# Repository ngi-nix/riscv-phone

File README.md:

# RISC-V Phone

This flake packages the firmware for the Freedom E310 and the Espressif ESP32 SoCs.

It is currently based against $HEAD of upstream for the [source files](http://majstor.org/gitweb/?p=rvPhone.git;a=tree).

If anything breaks, you can always pin the `riscvphone-src` input to a working revision:

```
url = "git://majstor.org/rvPhone.git?rev=38e19a65fda7a37688320b4b732eb1113bbcbad7";
```
You may find more information about this project [here](http://majstor.org/rvphone/) and [here](http://majstor.org/rvphone/build.html).

For further details, please refer to the documentation in the flake itself.

## Building

To build the firmware for each SoC (and possibly also flash it), type `nix build .#fe310` or `nix build .#esp32`.

## Developing

You can enter a developer shell by typing `nix develop .#fe310` or `nix develop .#esp32`. 

Navigate into `fw/fe310` or `fw/esp32` and type `make` to compile. Typing `make clean` will delete the compiled files.

When typing `make` in `fw/esp32`, a configuration menu will open if no `sdkconfig` configuration file exists, even if empty. You can manually choose the configuration values in this menu at any time by typing `make menuconfig` or pass them automatically via the [sdkconfig.defaults](https://docs.espressif.com/projects/esp-idf/en/latest/esp32/api-reference/kconfig.html#using-sdkconfig-defaults) file.

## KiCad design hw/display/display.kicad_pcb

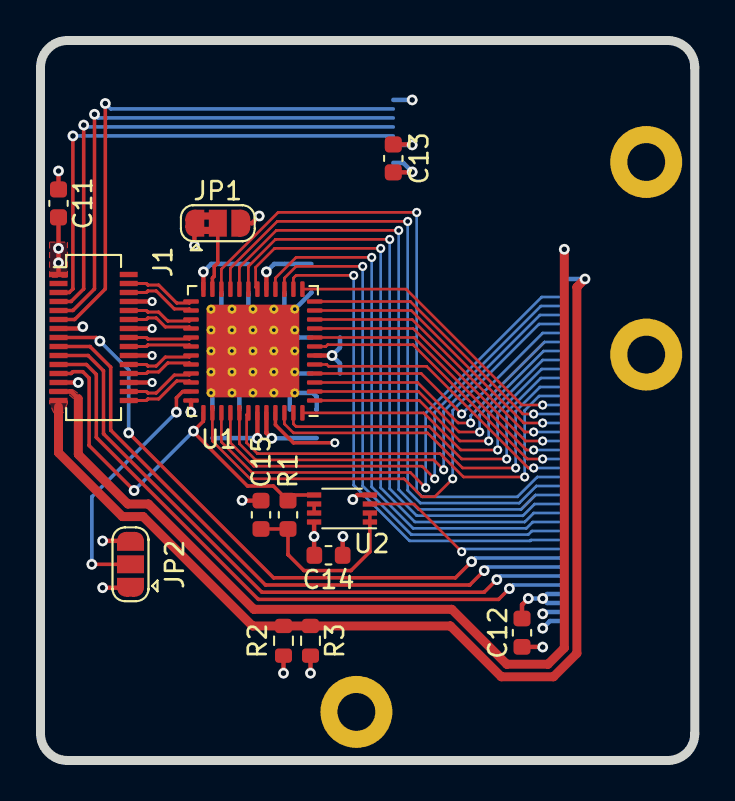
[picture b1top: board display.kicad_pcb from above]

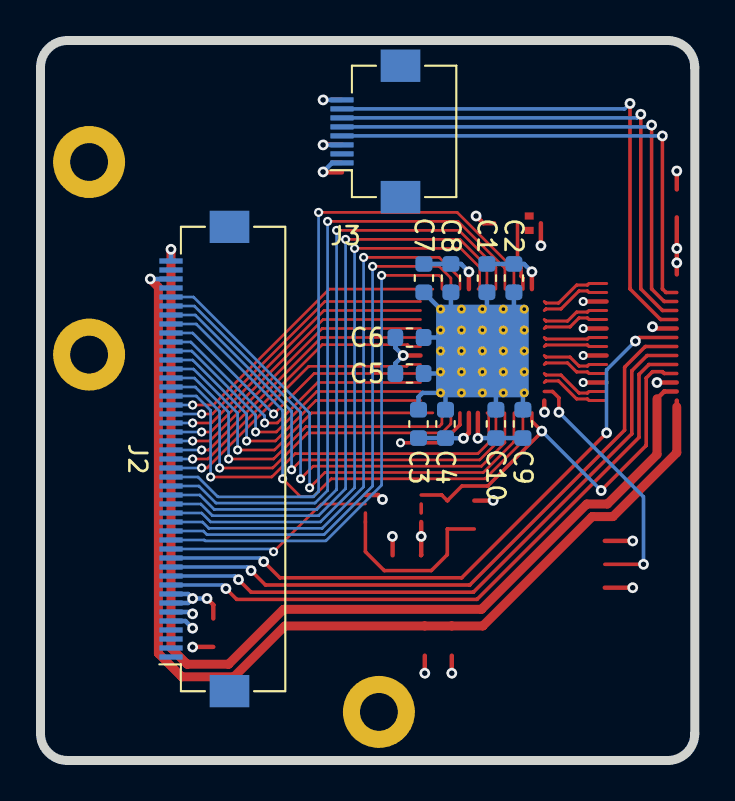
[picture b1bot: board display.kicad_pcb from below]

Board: 4 copper layers, 36.3 x 40.0 mm, 28 parts (12 on the bottom side), 56 nets.

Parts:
C1, C3, C5, C7, C9, C12, C13, C14, C15: 0.1uF; C_0603_1608Metric
C2, C4, C6, C8, C10: 0.01uF; C_0603_1608Metric
C11: 10uF; C_0603_1608Metric
J1: Input; Molex_SlimStack_55560-0301_2x15_P0.50mm_Vertical
J2: Display; Hirose_FH12-45S-0.5SH_1x45-1MP_P0.50mm_Horizontal
J3: Touch; Hirose_FH12-8S-0.5SH_1x08-1MP_P0.50mm_Horizontal
J4, J5, J6: Spacer
JP1: CLK_POL; SolderJumper-3_P1.3mm_Bridged2Bar12_RoundedPad1.0x1.5mm
JP2: SLEW; SolderJumper-3_P1.3mm_Open_RoundedPad1.0x1.5mm
R1: 10K; R_0603_1608Metric
R2, R3: DNP; R_0603_1608Metric
U1: SN65LVDS822; QFN-48-1EP_7x7mm_P0.5mm_EP5.15x5.15mm_ThermalVias
U2: 74AUP2G132DC; VSSOP-8_2.3x2mm_P0.5mm

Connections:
+3V3: C1.1, C2.1, C3.1, C4.1, C5.1, C6.1, C7.1, C8.1, C9.1, C10.1, C11.1, C12.1, C13.1, C14.1, J1.1, J2.7, J2.8, J3.3, JP1.1, JP2.1, U1.6, U1.17, U1.24, U1.43, U1.44, U2.8
/DISP_B0: J2.37, U1.4
/DISP_B1: J2.36, U1.3
/DISP_B2: J2.35, U1.2
/DISP_B3: J2.34, U1.1
/DISP_B4: J2.33, U1.48
/DISP_B5: J2.32, U1.47
/DISP_B6: J2.31, U1.46
/DISP_B7: J2.30, U1.42
/DISP_DE: J2.38, U1.38
/DISP_G0: J2.29, U1.13
/DISP_G1: J2.28, U1.12
/DISP_G2: J2.27, U1.11
/DISP_G3: J2.26, U1.10
/DISP_G4: J2.25, U1.9
/DISP_G5: J2.24, U1.8
/DISP_G6: J2.23, U1.7
/DISP_G7: J2.22, U1.5
/DISP_HSYNC: J2.40, U1.40
/DISP_PCLK: J2.39, U1.41
/DISP_R0: J2.21, U1.22
/DISP_R1: J2.20, U1.21
/DISP_R2: J2.19, U1.20
/DISP_R3: J2.18, U1.19
/DISP_R4: J2.17, U1.18
/DISP_R5: J2.16, U1.16
/DISP_R6: J2.15, U1.15
/DISP_R7: J2.14, U1.14
/DISP_RST: J2.13, U2.3
/DISP_VSYNC: J2.41, U1.39
/LVDS_A0N: J1.4, U1.25
/LVDS_A0P: J1.6, U1.26
/LVDS_A1N: J1.10, U1.27
/LVDS_A1P: J1.12, U1.28
/LVDS_A2N: J1.16, U1.29
/LVDS_A2P: J1.18, U1.30
/LVDS_A3N: J1.28, U1.33
/LVDS_A3P: J1.30, U1.34
/LVDS_CLKN: J1.22, U1.31
/LVDS_CLKP: J1.24, U1.32
CTP.INT: J1.9, J3.6
CTP.RST: J1.11, J3.7
CTP.SCL: J1.5, J3.4
CTP.SDA: J1.7, J3.5
ENABLE: J1.23, R1.2, U1.37, U2.5
GND: C1.2, C2.2, C3.2, C4.2, C5.2, C6.2, C7.2, C8.2, C9.2, C10.2, C11.2, C12.2, C13.2, C14.2, C15.2, J1.8, J1.13, J1.14, J1.20, J1.25, J1.26, J2.5, J2.6, J3.1, J3.8, J4.1, J5.1, J6.1, JP1.3, JP2.3, R2.2, R3.2, U1.36, U1.45, U1.49, U2.4
LED_A: J1.27, J2.45
LED_K: J1.29, J2.43, R2.1, R3.1
unnamed: C15.1, R1.1, U2.1, U2.2
unnamed: JP1.2, U1.23
unnamed: JP2.2, U1.35
unnamed: U2.6, U2.7
SPI.CS: J1.15, J2.12
SPI.MISO: J1.21, J2.9
SPI.MOSI: J1.19, J2.10
SPI.SCK: J1.17, J2.11

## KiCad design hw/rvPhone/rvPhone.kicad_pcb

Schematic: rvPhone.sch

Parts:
C1: 1uF; C_0603_1608Metric
C2: 0.047uF; C_0603_1608Metric
C3: 4.7uF; C_0603_1608Metric
C4, C5, C6, C7, C8, C9, C10, C11, C21, C22, C36, C38, C41, C42, C50, C53, C54: 10uF; C_0603_1608Metric
C12: 47uF; C_0805_2012Metric
C13, C15, C16, C17, C18, C19, C20, C23, C24, C27, C28, C29, C30, C31, C32, C33, C34, C35, C37, C39, C40, C43, C44, C45, C46: 0.1uF; C_0603_1608Metric
C14: 0.01uF; C_0603_1608Metric
C25, C26: 10pF; C_0603_1608Metric
C51, C52, C55: 22uF; C_0805_2012Metric
D1: B5817WS; D_SOD-323
D2: LED; LED_0603_1608Metric
J1: USB_OTG; GCT_MicroUSB-USB3080
J2: BATT; PinHeader_1x02_P2.54mm_Vertical
J3: +5V; PinHeader_1x02_P2.54mm_Vertical
J4: AudioJack; 35RASMT4BHNTRX
J5: SPEAKER; PinHeader_1x04_P2.54mm_Vertical
J6: Ext Audio; Molex_SlimStack_54722-0164_2x08_P0.50mm_Vertical
JP1: AUDIO PWR; SolderJumper-3_P1.3mm_Open_RoundedPad1.0x1.5mm
L1: 2.2uH; L_Vishay_IHLP-2525
L2: 2.2uH; Coilcraft-LPS3015
L3: 1uH; Coilcraft-XAL40
R1: 260R; R_0603_1608Metric
R2: 5.23K; R_0603_1608Metric
R3: 30.1K; R_0603_1608Metric
R4: 2.2K; R_0603_1608Metric
R5: 560K; R_0603_1608Metric
R6: 180K; R_0603_1608Metric
R7, R8, R9, R10, R11, R15, R16, R18, R19, R20, R21, R22, R23, R24, R25, R26, R30, R34, R35: 100K; R_0603_1608Metric
R12: 100R; R_0603_1608Metric
R13, R14, R33: 10K; R_0603_1608Metric
R17, R28, R29: 47K; R_0603_1608Metric
R27: 210K; R_0603_1608Metric
R31: 50K; R_0603_1608Metric
R32: 0R; R_0603_1608Metric
SW1: RESET; SW_SPST_PTS810
SW2: WAKE; Panasonic_EVPAE
TP2: PMU_OUT0; TestPoint_Pad_D1.5mm
U1: BQ25895; Texas_S-PWQFN-N24_EP2.7x2.7mm_ThermalVias
U2: TPS62293; TPS62290
U3: TPS630250
U4: FE310-G002; QFN-48-1EP_6x6mm_P0.4mm_EP4.2x4.2mm_ThermalVias
U5: IS25LP128-JKLE; WSON-8-1EP_6x5mm_P1.27mm_EP3.4x4mm
U6: SN74LVC2G07DCK; Texas_R-PDSO-G6
U7: TMUX1574RSV; UQFN-16_1.8x2.6mm_P0.4mm
U8, U9: 74HC00; DHVQFN-14_2.5x3.0mm_P0.5mm_EP1.0x1.5mm
U10, U11: 74HC595; DHVQFN-16_2.5x3.5mm_P0.5mm_EP1.0x2.0mm
U12: ICS-43434
U13, U14: MAX98357A; TQFN-16-1EP_3x3mm_P0.5mm_EP1.23x1.23mm_ThermalVias
U15, U16: MAX14689A; TDFN-10-1EP_2x2.5mm_P0.4mm_EP1.3x1.4mm_ThermalVias
U17: SN74LVC1G04DCK; Texas_R-PDSO-G5
U18: TMUX1119DCK; Texas_R-PDSO-G6
U19: 74LVC1G02; Texas_R-PDSO-G5
U20: SN74LVC2G66DCU; VSSOP-8_2.3x2mm_P0.5mm
X1: SiT1533
Y1: 16MHz; TXC_7M

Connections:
+1V8: C9.1, C19.1, C20.1, C21.1, C55.1, L2.2, R12.1, U2.3 (FB), U4.6 (VDD), U4.30 (VDD), U4.46 (VDD); also elsewhere on the board
+VSYS: C4.1, C5.1, C8.1, C10.1, D2.2 (A), L1.2, U1.8 (OTG), U1.15 (SYS), U1.16 (SYS), U2.4 (EN), U2.5 (VIN), U3.4 (VIN), U3.5 (VIN), U3.6 (VIN), U3.7 (VINA), U3.8 (EN); also elsewhere on the board
/AON_PMU_OUT_0: TP2.1, U4.22 (AON_PMU_OUT_0)
/AON_PMU_OUT_1: U4.17 (AON_PMU_OUT_1)
/AUDIO_OUT_L+: U13.9 (OUTP), U15.3
/AUDIO_OUT_L-: U13.10 (OUTN), U15.10
/AUDIO_OUT_R+: U14.9 (OUTP), U16.3
/AUDIO_OUT_R-: U14.10 (OUTN), U16.10
/BQ_QON: U1.12 (/QON), U6.4 (2Y)
/BQ_SW: C2.1, D1.2 (A), L1.1, U1.19 (SW), U1.20 (SW)
/EXT_AUDIO_EN: J6.10, U19.4
/HP_DET: J4.RN, J4.TN, R30.1, U17.2 (A)
/HP_L: C42.2, U15.5
/HP_R: C41.2, U16.5
/MIC_CLK: R23.2, U7.11 (S4B), U8.1, U9.12, U9.13, U12.4 (SCK)
/MIC_SD: U12.6 (SD), U20.2
/MIC_WS: R21.2, U7.1 (S1B), U12.1 (WS)
/PLL_AVDD: C23.1, C24.1, R12.2, U4.7 (PLL_AVDD)
/PLL_AVSS: C23.2, C24.2, U4.8 (PLL_AVSS)
/PSD_LFALTCLK: U4.20 (AON_PSD_LFALTCLK), X1.3 (CLKOUT)
/QSPI_CLK: U4.48 (QSPI_CLK), U5.6 (SCK)
/QSPI_CS: R8.2, U4.5 (QSPI_CS), U5.1 (S#)
/QSPI_DQ_0: U4.4 (QSPI_DQ_0), U5.5 (MOSI/IO0)
/QSPI_DQ_1: U4.3 (QSPI_DQ_1), U5.2 (MISO/IO1)
/QSPI_DQ_2: U4.2 (QSPI_DQ_2), U5.3 (WP#/IO2)
/QSPI_DQ_3: R9.2, U4.1 (QSPI_DQ_3), U5.7 (HOLD#/IO3)
/RESET: C14.1, R10.1, SW1.2, U4.24 (AON_ERST_N), U6.6 (1Y)
/SD_IN: U7.4 (S2B), U11.9, U13.1 (DIN), U14.1 (DIN)
/SD_OUT: R22.2, U7.8 (S3B), U10.14, U20.1
/SPK_CLK: U9.11, U13.16 (BCLK), U14.16 (BCLK)
/SPK_EN: C39.1, C40.1, R27.2, U7.15 (SEL), U8.8, U9.4, U9.5, U13.4 (SD_MODE), U15.2, U16.2, U19.1
/SPK_GAIN: U13.2 (GAIN_SLOT), U14.2 (GAIN_SLOT), U18.5
/SPK_GAIN_SEL: U9.8, U18.1
/SPK_L+: J5.1, J6.5, J6.7, U15.1
/SPK_L-: J5.2, J6.9, J6.11, U15.8
/SPK_R+: J5.3, U16.1
/SPK_R-: J5.4, U16.8
/XTAL_XI: C25.1, U4.9 (16M_XTAL_XI), Y1.1
/XTAL_XO: C26.1, U4.10 (16M_XTAL_XO), Y1.2
/~HP_DET: U9.9, U15.7, U16.7, U17.4 (Y)
BQ.INT: U1.7 (INT); also elsewhere on the board
BT81X.AUDIO: J6.6; also elsewhere on the board
BT81X.GPIO2: U9.10, U19.2; also elsewhere on the board
BT81X.INT: R16.1, U7.12 (S4A); also elsewhere on the board
CTP.RST: R15.1, U7.16 (S1A); also elsewhere on the board
DISP_CS: U9.3; also elsewhere on the board
GND: C1.2, C3.2, C4.2, C5.2, C6.2, C7.2, C8.2, C9.2, C10.2, C11.2, C12.2, C13.2, C14.2, C15.2, C16.2, C17.2, C18.2, C19.2, C20.2, C21.2, C22.2, C25.2, C26.2, C27.2, C28.2, C29.2, C30.2, C31.2, C32.2, C33.2, C34.2, C35.2, C36.2, C37.2, C38.2, C39.2, C40.2, C43.2, C44.2, C45.2, C46.2, C50.2, C51.2, C52.2, C53.2, C54.2, C55.2, J1.5 (GND), J2.2, J3.2, J4.S, J6.1, J6.3, R1.2, R3.2, R6.2, R18.1, R19.1, R20.1, R21.1, R22.1, R23.1, R26.1, R28.2, R29.2, R32.2, R33.2, R34.1, R35.1, SW1.1, SW2.1, U1.9 (/CE), U1.17 (PGND), U1.18 (PGND), U1.25 (EP), U2.2 (MODE), U2.6 (GND), U2.7 (EP), U3.2 (PGND), U3.9 (GND), U3.10 (PFM), U4.21 (AON_PSD_LFCLKSEL), U4.49 (GND), U5.4 (VSS), U5.9 (EP), U6.2 (GND), U7.6 (GND), U7.13 (/EN), U8.7 (GND), U8.15, U9.7 (GND), U9.15, U10.8, U10.12, U10.17, U11.8, U11.12, U11.17, U12.2 (LR), U12.3 (GND), U13.3 (GND), U13.11 (GND), U13.15 (GND), U13.17 (EP), U14.3 (GND), U14.11 (GND), U14.15 (GND), U14.17 (EP), U15.4, U15.9, U15.11, U16.4, U16.9, U16.11, U17.3 (GND), U18.3, U19.3, U20.3, U20.4, U20.5, U20.6, X1.2 (GND), Y1.3; also elsewhere on the board
GPIO_0: U4.25 (GPIO_0/PWM0.0); also elsewhere on the board
GPIO_16: U4.38 (GPIO_16/UART0.RX), U7.7 (D3)
GPIO_17: U4.39 (GPIO_17/UART0.TX), U7.5 (D2)
GPIO_18: R19.2, U4.40 (GPIO_18), U8.5, U8.12, U8.13
GPIO_20: U4.42 (GPIO_20/PWM1.0); also elsewhere on the board
GPIO_22: U4.44 (GPIO_22/PWM1.3); also elsewhere on the board
GPIO_23: R18.2, U4.45 (GPIO_23); also elsewhere on the board
I2C0.SCL: R13.2, U1.5 (SCL), U4.37 (GPIO_13/PWM2.3); also elsewhere on the board
I2C0.SDA: R14.2, U1.6 (SDA), U4.36 (GPIO_12/PWM2.2); also elsewhere on the board
JTAG_TCK: U4.13 (JTAG_TCK); also elsewhere on the board
JTAG_TDI: U4.16 (JTAG_TDI); also elsewhere on the board
JTAG_TDO: U4.14 (JTAG_TDO); also elsewhere on the board
JTAG_TMS: U4.15 (JTAG_TMS); also elsewhere on the board
JTAG_TRST_N: R7.2, U6.1 (1A); also elsewhere on the board
unnamed: C2.2, U1.21 (BTST)
unnamed: C3.1, R2.1, U1.22 (REGN)
unnamed: C6.1, C7.1, J2.1, U1.13 (BAT), U1.14 (BAT)
unnamed: C41.1, J4.R, R28.1
unnamed: C42.1, J4.T, R29.1
unnamed: D2.1 (K), R4.2
unnamed: L2.1, U2.1 (SW)
unnamed: L3.1, U3.3 (L1)
unnamed: L3.2, U3.1 (L2)
unnamed: R1.1, U1.10 (ILIM)
unnamed: R2.2, R3.1, R33.1, U1.11 (TS)
unnamed: R4.1, U1.4 (STAT)
unnamed: R5.2, R6.1, U3.11 (FB)
unnamed: R27.1, U14.4 (SD_MODE)
unnamed: R31.2, U18.6
unnamed: R32.1, U18.4
unnamed: U1.2 (D+), U1.3 (D-)
unnamed: U8.3, U8.4
unnamed: U8.10, U8.11
unnamed: U9.2, U9.6
unnamed: U10.9, U11.14
unnamed: U8.6, U10.11, U11.11
PWM0.1: U4.26 (GPIO_1/PWM0.1), U7.10 (D4)
PWM1.1: U4.41 (GPIO_19/PWM1.1), U7.2 (D1)
PWM1.2: R17.2, U4.43 (GPIO_21/PWM1.2), U8.2, U8.9, U20.7
PWM2.1: R20.2, U4.35 (GPIO_11/PWM2.1), U9.1, U13.14 (LRCLK), U14.14 (LRCLK)
SPI1.MISO: R24.2, U4.29 (GPIO_4/SPI1.MISO); also elsewhere on the board
SPI1.MOSI: R25.2, U4.28 (GPIO_3/SPI1.MOSI/PWM0.3); also elsewhere on the board
SPI1.SCK: R26.2, U4.31 (GPIO_5/SPI1.SCK); also elsewhere on the board
SPI1.SS0: U4.27 (GPIO_2/SPI1.SS0/PWM0.2); also elsewhere on the board
SPI1.SS2: U4.33 (GPIO_9/SPI1.SS2); also elsewhere on the board
SPI1.SS3: U4.34 (GPIO_10/SPI1.SS3/PWM2.0); also elsewhere on the board
UART0.RXD: R35.2, U7.9 (S3A); also elsewhere on the board
UART0.TXD: R34.2, U7.3 (S2A); also elsewhere on the board
USB_D+: J1.3 (D+); also elsewhere on the board
USB_D-: J1.2 (D-); also elsewhere on the board
VBUS: C1.1, C50.1, J1.1 (VBUS), U1.1 (VBUS); also elsewhere on the board
WAKE: R11.1, SW2.2, U4.18 (AON_PMU_DWAKEUP_N), U6.3 (2A); also elsewhere on the board

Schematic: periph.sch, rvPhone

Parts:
C201, C204, C205, C206, C207, C208, C209, C210, C211, C212, C213, C214, C219, C220, C223, C224, C226, C227, C229, C230, C231: 0.1uF; C_0603_1608Metric
C202, C228: 22uF; C_0805_2012Metric
C203, C221, C222: 1uF; C_0603_1608Metric
C215, C216, C217: 33pF; C_0603_1608Metric
C218: 470uF; CP_EIA-7343-31_Kemet-D
C225: 0.01uF; C_0603_1608Metric
J201: Modem; TE_mPCIe-1775862
J202: SIM_Card; Wurth_NanoSIM-693043020611
J203: Motor; SolderWirePad_1x02_SMD_1x2mm
J204: Micro_SD_Card_Det; Molex_MicroSD-5027740891
J205: Prog; Hirose_FH12-12S-0.5SH_1x12-1MP_P0.50mm_Horizontal
J206: Expansion; Molex_SlimStack_54722-0164_2x08_P0.50mm_Vertical
J207: Camera; Molex_SlimStack_54722-0164_2x08_P0.50mm_Vertical
J208, J209: Spacer; Spacer_small
JP201: PCM_EN; SolderJumper-3_P1.3mm_Bridged2Bar12_RoundedPad1.0x1.5mm
JP202: SIMCom_EN; SolderJumper-3_P1.3mm_Bridged2Bar12_RoundedPad1.0x1.5mm
JP203: Q.DTR; SolderJumper-2_P1.3mm_Open_RoundedPad1.0x1.5mm
JP204: Q.RI; SolderJumper-2_P1.3mm_Open_RoundedPad1.0x1.5mm
JP205: Q.RXD; SolderJumper-2_P1.3mm_Open_RoundedPad1.0x1.5mm
JP206: Q.TXD; SolderJumper-2_P1.3mm_Open_RoundedPad1.0x1.5mm
R201, R209: 10K; R_0603_1608Metric
R202, R203, R207: 47K; R_0603_1608Metric
R204, R205, R206: 22R; R_0603_1608Metric
R208: 4.7K; R_0603_1608Metric
SW201: ESP32_RST; SW_SPST_PTS810
SW202: MODEM_RST; SW_SPST_PTS810
U201: ESP32-WROOM
U202: SN74CBTLV3125RGY; Texas_S-PVQFN-N14_ThermalVias
U203, U204: TXB0104RGY; Texas_S-PVQFN-N14_ThermalVias
U205: DRV2605LDGS; VSSOP-10_3x3mm_P0.5mm
U206: LSM9DS1; LGA-24L_3x3.5mm_P0.43mm
U207: FT230XQ; QFN-16-1EP_4x4mm_P0.65mm_EP2.1x2.1mm
U208: TMUX154ERSW; UQFN-10_1.4x1.8mm_P0.4mm

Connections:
+1V8: C206.1, C208.1, JP201.1, JP202.1, U203.1 (VCCA), U204.1 (VCCA); also elsewhere on the board
+VSYS: J207.2, J207.4; also elsewhere on the board
/periph/ESP32_EN: C203.1, C219.1, R201.2, SW201.1, U201.3 (EN)
/periph/ESP32_PCM_CLK: U201.9 (IO33), U203.13 (B1)
/periph/ESP32_PCM_DI: U201.6 (IO34), U203.12 (B2)
/periph/ESP32_PCM_DO: U201.24 (IO2), U203.11 (B3)
/periph/ESP32_PCM_SYNC: U201.26 (IO4), U203.10 (B4)
/periph/ESP32_UART2_DTR: JP203.1, U201.8 (IO32), U204.12 (B2)
/periph/ESP32_UART2_RI: JP204.1, U201.7 (IO35), U204.13 (B1)
/periph/ESP32_UART2_RXD: JP206.1, U201.28 (IO17), U204.11 (B3)
/periph/ESP32_UART2_TXD: JP205.1, U201.27 (IO16), U204.10 (B4)
/periph/ESP32_VSPI_MISO: U201.31 (IO19), U202.5 (2A)
/periph/ESP32_VSPI_MOSI: U201.37 (IO23), U202.9 (3A)
/periph/ESP32_VSPI_SCK: U201.30 (IO18), U202.12 (4A)
/periph/ESP32_VSPI_SS0: R202.2, U201.29 (IO5), U202.3 (1B)
/periph/PCM_CLK: J201.45, U203.2 (A1)
/periph/PCM_DI: J201.49, U203.4 (A3)
/periph/PCM_DO: J201.47, U203.3 (A2)
/periph/PCM_SYNC: J201.51, U203.5 (A4)
/periph/PERST: C220.1, J201.22, SW202.1
/periph/Quectel_UART_DTR: J201.31, JP203.2
/periph/Quectel_UART_RI: J201.17, JP204.2, U204.5 (A4)
/periph/Quectel_UART_RXD: J201.11, JP205.2
/periph/Quectel_UART_TXD: J201.13, JP206.2
/periph/SIMCom_UART_DTR: J201.46, U204.3 (A2)
/periph/SIMCom_UART_RI: J201.44, U204.2 (A1)
/periph/SIMCom_UART_TXD: J201.19, U204.4 (A3)
/periph/USB_CBUS0: U207.12 (CBUS0), U208.8 (/EN)
/periph/USB_CBUS1: U207.11 (CBUS1), U208.10 (SEL)
/periph/USB_CBUS3: R208.2, R209.1, U207.14 (CBUS3)
/periph/USB_RXD: U207.2 (RXD), U208.5 (B)
/periph/USB_TXD: U207.15 (TXD), U208.3 (A)
BQ.INT: U201.10 (IO25); also elsewhere on the board
BT81X.GPIO0: J207.10; also elsewhere on the board
BT81X.GPIO3: U205.4 (IN/TRIG); also elsewhere on the board
ESP32.HSPI.MISO: U201.14 (IO12); also elsewhere on the board
ESP32.HSPI.MOSI: U201.16 (IO13); also elsewhere on the board
ESP32.HSPI.SCK: U201.13 (IO14); also elsewhere on the board
ESP32.HSPI.SS0: U201.23 (IO15); also elsewhere on the board
ESP32.IO26: U201.11 (IO26); also elsewhere on the board
ESP32.IO27: U201.12 (IO27); also elsewhere on the board
ESP32.UART0.RXD: J205.1, U201.34 (RXD0), U208.2 (A1)
ESP32.UART0.TXD: J205.2, U201.35 (TXD0), U208.6 (B1)
GND: C201.2, C202.2, C203.2, C204.2, C205.2, C206.2, C207.2, C208.2, C209.2, C210.2, C211.2, C212.2, C213.2, C214.2, C215.2, C216.2, C217.2, C218.2, C219.2, C220.2, C221.2, C222.2, C223.2, C224.2, C225.2, C226.2, C227.2, C228.2, C229.2, C230.2, C231.2, J201.4, J201.9, J201.15, J201.18, J201.21, J201.26, J201.27, J201.29, J201.34, J201.35, J201.37, J201.40, J201.43, J201.50, J201.53, J202.5 (GND), J204.6, J204.11, J205.3, J205.9, J206.6, J206.11, J206.16, J207.6, J207.11, J207.16, J208.1, J209.1, JP201.3, JP202.3, R209.2, SW201.2, SW202.2, U201.1 (GND), U201.15 (GND), U201.38 (GND), U201.39 (EP), U202.2 (1A), U202.7 (GND), U202.15 (EP), U203.7 (GND), U203.15 (Pad), U204.7 (GND), U204.15 (Pad), U205.8 (GND), U206.14 (RES), U206.15 (RES), U206.16 (RES), U206.17 (RES), U206.18 (RES), U206.19 (GND), U206.20 (GND), U207.3 (GND), U207.4 (~CTS), U207.13 (GND), U207.17 (GND), U208.4 (GND); also elsewhere on the board
GPIO_0: J204.2, R207.2; also elsewhere on the board
GPIO_20: U201.36 (IO22); also elsewhere on the board
GPIO_22: U201.33 (IO21); also elsewhere on the board
I2C0.SCL: J206.14, J207.14, U205.2 (SCL), U206.2 (SCL/SPC); also elsewhere on the board
I2C0.SDA: J206.12, J207.12, U205.3 (SDA), U206.4 (SDA/SDI/SDO); also elsewhere on the board
JTAG_TCK: J205.4; also elsewhere on the board
JTAG_TDI: J205.7; also elsewhere on the board
JTAG_TDO: J205.5; also elsewhere on the board
JTAG_TMS: J205.6; also elsewhere on the board
JTAG_TRST_N: J205.8; also elsewhere on the board
unnamed: C214.1, J201.8, J202.1 (VCC)
unnamed: C215.1, J202.2 (RST), R206.1
unnamed: C216.1, J202.3 (CLK), R205.1
unnamed: C217.1, J202.7 (I/O), R204.1
unnamed: C222.1, U205.1 (REG)
unnamed: C225.1, U206.21 (CAP)
unnamed: C226.1, U206.24 (C1)
unnamed: J201.10, R204.2
unnamed: J201.12, R205.2
unnamed: J201.14, R206.2
unnamed: J203.1, U205.7 (OUT+)
unnamed: J203.2, U205.9 (OUT-)
unnamed: JP201.2, U203.8 (OE)
unnamed: JP202.2, U204.8 (OE)
SPI1.MISO: J204.7, J206.7, J207.7, U202.6 (2B); also elsewhere on the board
SPI1.MOSI: J204.3, J206.5, J207.5, U202.8 (3B); also elsewhere on the board
SPI1.SCK: J204.5, J206.9, J207.9, U202.11 (4B); also elsewhere on the board
SPI1.SS0: R203.2, U202.1 (/1OE), U202.4 (/2OE), U202.10 (/3OE), U202.13 (/4OE); also elsewhere on the board
SPI1.SS2: J207.8; also elsewhere on the board
UART0.RXD: J205.11, J206.15, U208.1 (A0); also elsewhere on the board
UART0.TXD: J205.10, J206.13, U208.7 (B0); also elsewhere on the board
USB_D+: U207.6 (USBDP); also elsewhere on the board
USB_D-: U207.7 (USBDM); also elsewhere on the board
VBUS: R208.1; also elsewhere on the board
WAKE: U201.25 (IO0); also elsewhere on the board
iMX8.USB1.D_N: J201.36; also elsewhere on the board
iMX8.USB1.D_P: J201.38; also elsewhere on the board

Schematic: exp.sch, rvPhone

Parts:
C301: 4.7uF; C_0603_1608Metric
C302, C303, C304, C305, C306, C307, C308, C309, C310, C311, C312, C313, C319: 0.1uF; C_0603_1608Metric
C314, C315, C316, C317, C318, C320: 22uF; C_0805_2012Metric
J301: iMX8; TE_SODIMMDDR3-2013289
J302: Micro_SD_Card_Det; Molex_MicroSD-5027740891
J303: Console; Hirose_FH12-6S-0.5SH_1x06-1MP_P0.50mm_Horizontal
JP301: USB_VBUS; SolderJumper-2_P1.3mm_Open_RoundedPad1.0x1.5mm
JP302: USB_ID; SolderJumper-2_P1.3mm_Open_RoundedPad1.0x1.5mm
R301, R302: 47K; R_0603_1608Metric
R303, R304: 10K; R_0603_1608Metric
R305, R306, R307: 100K; R_0603_1608Metric
SW301: iMX8_ALT_BOOT; SW_SPST_PTS810
SW302: iMX8_RST; SW_SPST_PTS810
SW303: iMX8_PWR; SW_SPST_PTS810

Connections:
+VSYS: C302.1, C303.1, C304.1, C305.1, C306.1, C307.1, C308.1, C309.1, C310.1, C311.1, C312.1, C313.1, C314.1, C315.1, C316.1, C317.1, C318.1, J301.10 (PIN10), J301.28 (PIN28), J301.46 (PIN46), J301.64 (PIN64), J301.78 (PIN78), J301.96 (PIN96), J301.114 (PIN114), J301.132 (PIN132), J301.150 (PIN150), J301.168 (PIN168), J301.186 (PIN186), J301.204 (PIN204); also elsewhere on the board
/exp/ALT_BOOT: J301.185 (PIN185), SW301.1
/exp/POWER: J301.165 (PIN165), SW303.1
/exp/RESET: J301.171 (PIN171), SW302.1
/exp/SD2_CLK: J301.80 (PIN80), J302.5
/exp/SD2_CMD: J301.82 (PIN82), J302.3
/exp/SD2_DAT0: J301.84 (PIN84), J302.7
/exp/SD2_DAT1: J301.86 (PIN86), J302.8
/exp/SD2_DAT2: J301.88 (PIN88), J302.1
/exp/SD2_DAT3: J301.90 (PIN90), J302.2
/exp/SD2_DET: J301.61 (PIN61), J302.9, R301.2
/exp/UART3_RX: J301.117 (PIN117), J303.3
/exp/UART3_TX: J301.111 (PIN111), J303.4
ESP32.HSPI.MISO: J301.15 (PIN15); also elsewhere on the board
ESP32.HSPI.MOSI: J301.11 (PIN11); also elsewhere on the board
ESP32.HSPI.SCK: J301.13 (PIN13); also elsewhere on the board
ESP32.HSPI.SS0: J301.17 (PIN17), R302.2; also elsewhere on the board
ESP32.IO26: J301.7 (PIN7); also elsewhere on the board
ESP32.IO27: J301.9 (PIN9); also elsewhere on the board
GND: C301.2, C302.2, C303.2, C304.2, C305.2, C306.2, C307.2, C308.2, C309.2, C310.2, C311.2, C312.2, C313.2, C314.2, C315.2, C316.2, C317.2, C318.2, C319.2, C320.2, J301.1 (PIN1), J301.19 (PIN19), J301.37 (PIN37), J301.55 (PIN55), J301.67 (PIN67), J301.71 (PIN71), J301.87 (PIN87), J301.105 (PIN105), J301.123 (PIN123), J301.141 (PIN141), J301.159 (PIN159), J301.177 (PIN177), J302.6, J302.10, J302.11, J303.5, J303.6, JP302.1, R306.1, R307.1, SW302.2, SW303.2; also elsewhere on the board
unnamed: C301.1, J301.183 (PIN183)
iMX8.GPIO5.IO28: J301.5 (PIN5), R306.2; also elsewhere on the board
iMX8.GPIO5.IO29: J301.3 (PIN3), R305.2; also elsewhere on the board
iMX8.I2C3.SCL: J301.43 (PIN43), R303.2; also elsewhere on the board
iMX8.I2C3.SDA: J301.49 (PIN49), R304.2; also elsewhere on the board
iMX8.LVDS0.A0N: J301.41 (PIN41); also elsewhere on the board
iMX8.LVDS0.A0P: J301.39 (PIN39); also elsewhere on the board
iMX8.LVDS0.A1N: J301.47 (PIN47); also elsewhere on the board
iMX8.LVDS0.A1P: J301.45 (PIN45); also elsewhere on the board
iMX8.LVDS0.A2N: J301.53 (PIN53); also elsewhere on the board
iMX8.LVDS0.A2P: J301.51 (PIN51); also elsewhere on the board
iMX8.LVDS0.A3N: J301.59 (PIN59); also elsewhere on the board
iMX8.LVDS0.A3P: J301.57 (PIN57); also elsewhere on the board
iMX8.LVDS0.CLKN: J301.35 (PIN35); also elsewhere on the board
iMX8.LVDS0.CLKP: J301.33 (PIN33); also elsewhere on the board
iMX8.PWM1: J301.200 (PIN200), R307.2; also elsewhere on the board
iMX8.USB1.D_N: J301.178 (PIN178); also elsewhere on the board
iMX8.USB1.D_P: J301.176 (PIN176); also elsewhere on the board
iMX8.USB1.ID: J301.174 (PIN174), JP302.2
iMX8.USB1.VBUS: J301.180 (PIN180), JP301.2

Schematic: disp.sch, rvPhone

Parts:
C401, C402, C415: 1uF; C_0603_1608Metric
C403, C406, C408, C411, C412, C413, C414, C416, C417, C419, C420, C422, C424, C426, C427, C428, C429, C430, C431, C432, C433, C434: 0.1uF; C_0603_1608Metric
C404, C418, C441: 10uF; C_0603_1608Metric
C409, C410: 10pF; C_0603_1608Metric
C421, C423, C425: 0.01uF; C_0603_1608Metric
D401: MBR0540; D_SOD-123
D402: 3SMAJ5935B-TP; D_SMA
J401: Display; Molex_SlimStack_54722-0304_2x15_P0.50mm_Vertical
J402, J403, J404: Spacer; Spacer_small
JP402: VOD_SEL; SolderJumper-3_P1.3mm_Bridged2Bar12_RoundedPad1.0x1.5mm
L401: 10uH; Murata-LQH66SN
R401, R402, R406, R407, R408, R409, R410: 47K; R_0603_1608Metric
R403: 22R; R_0603_1608Metric
R404: 15R; R_0603_1608Metric
R405: 68R; R_0603_1608Metric
U401: FAN5333BSX; SOT-23-5
U402: SN74LVC3G06DCU; VSSOP-8_2.4x2.1mm_P0.5mm
U403: BT817Q; QFN-64-1EP_9x9mm_P0.5mm_EP6x6mm_ThermalVias
U404: IS25LP128-JKLE; WSON-8-1EP_6x5mm_P1.27mm_EP3.4x4mm
U405: DS90C185; QFN-48-1EP_6x6mm_P0.4mm_EP4.6x4.6mm_ThermalVias
U406: TS3DV520ERUA; Texas_R-PWQFN-N42
U407: TMUX1574RSV; UQFN-16_1.8x2.6mm_P0.4mm
Y401: 12MHz; TXC_7M

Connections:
+1V8: C403.1, C414.1, C421.1, C422.1, C423.1, C424.1, C425.1, C426.1, C441.2, J401.3, JP402.3, R401.1, U402.8 (VCC), U403.28 (VCCIO2), U405.13 (VDDPLL), U405.25 (VDDTX), U405.48 (VDD); also elsewhere on the board
+VSYS: C404.1, L401.1, R402.1, U401.5 (VIN); also elsewhere on the board
/disp/BT81X_1V2: C415.1, C416.1, C417.1, C418.1, C419.1, U403.2 (VIN1V2), U403.25 (VOUT1V2), U403.57 (VIN1V2)
/disp/BT81X_QSPI_CLK: U403.14 (SPIMSCK), U404.6 (SCK)
/disp/BT81X_QSPI_CS: R408.2, U403.15 (SPIMCS), U404.1 (S#)
/disp/BT81X_QSPI_DQ_0: U403.16 (SPIMMOSI), U404.5 (MOSI/IO0)
/disp/BT81X_QSPI_DQ_1: U403.18 (SPIMMISO), U404.2 (MISO/IO1)
/disp/BT81X_QSPI_DQ_2: R410.2, U403.19 (SPIMIO2), U404.3 (WP#/IO2)
/disp/BT81X_QSPI_DQ_3: R409.2, U403.20 (SPIMIO3), U404.7 (HOLD#/IO3)
/disp/BT81X_X1: C409.1, U403.21 (X1/CLK), Y401.1
/disp/BT81X_X2: C410.1, U403.22 (X2), Y401.2
/disp/CTP_INT: J401.9, U407.7 (D3)
/disp/CTP_RST: J401.11, U407.10 (D4)
/disp/CTP_SCL: J401.5, U407.2 (D1)
/disp/CTP_SDA: J401.7, U407.5 (D2)
/disp/DISP_LVDS_A0N: J401.4, U406.15 (A9)
/disp/DISP_LVDS_A0P: J401.6, U406.14 (A8)
/disp/DISP_LVDS_A1N: J401.10, U406.11 (A7)
/disp/DISP_LVDS_A1P: J401.12, U406.10 (A6)
/disp/DISP_LVDS_A2N: J401.16, U406.9 (A5)
/disp/DISP_LVDS_A2P: J401.18, U406.8 (A4)
/disp/DISP_LVDS_A3N: J401.28, U406.3 (A1)
/disp/DISP_LVDS_A3P: J401.30, U406.2 (A0)
/disp/DISP_LVDS_CLKN: J401.22, U406.6 (A3)
/disp/DISP_LVDS_CLKP: J401.24, U406.5 (A2)
/disp/DS90_LVDS_A0N: U405.36 (TX0-), U406.21 (9B2)
/disp/DS90_LVDS_A0P: U405.35 (TX0+), U406.20 (8B2)
/disp/DS90_LVDS_A1N: U405.34 (TX1-), U406.23 (7B2)
/disp/DS90_LVDS_A1P: U405.33 (TX1+), U406.24 (6B2)
/disp/DS90_LVDS_A2N: U405.32 (TX2-), U406.27 (5B2)
/disp/DS90_LVDS_A2P: U405.31 (TX2+), U406.28 (4B2)
/disp/DS90_LVDS_A3N: U405.28 (TX3-), U406.36 (1B2)
/disp/DS90_LVDS_A3P: U405.27 (TX3+), U406.37 (0B2)
/disp/DS90_LVDS_CLKN: U405.30 (TXCLK-), U406.32 (3B2)
/disp/DS90_LVDS_CLKP: U405.29 (TXCLK+), U406.33 (2B2)
BT81X.AUDIO: U403.26 (AUDIO_L); also elsewhere on the board
BT81X.B0: U403.47 (B0), U405.4 (D12)
BT81X.B1: U403.46 (B1), U405.5 (D13)
BT81X.B2: U403.45 (B2), U405.7 (D14)
BT81X.B3: U403.44 (B3), U405.8 (D15)
BT81X.B4: U403.43 (B4), U405.9 (D16)
BT81X.B5: U403.42 (B5), U405.10 (D17)
BT81X.B6: U403.41 (B6), U405.20 (D25)
BT81X.B7: U403.40 (B7), U405.21 (D26)
BT81X.BL_PWM: U402.3 (2A), U403.34 (BL_PWM)
BT81X.DE: U403.35 (DE), U405.14 (D20)
BT81X.DISP: U403.38 (DISP), U405.37 (PDB), U406.12 (SEL), U407.15 (SEL)
BT81X.G0: U403.56 (G0), U405.45 (D6)
BT81X.G1: U403.55 (G1), U405.46 (D7)
BT81X.G2: U403.54 (G2), U405.47 (D8)
BT81X.G3: U403.53 (G3), U405.1 (D9)
BT81X.G4: U403.52 (G4), U405.2 (D10)
BT81X.G5: U403.51 (G5), U405.3 (D11)
BT81X.G6: U403.50 (G6), U405.18 (D23)
BT81X.G7: U403.49 (G7), U405.19 (D24)
BT81X.GPIO0: U403.7 (GPIO0/IO2); also elsewhere on the board
BT81X.GPIO1: J401.23, U403.8 (GPIO1/IO3)
BT81X.GPIO2: U403.10 (GPIO2); also elsewhere on the board
BT81X.GPIO3: U403.13 (GPIO3); also elsewhere on the board
BT81X.HSYNC: U403.37 (HSYNC), U405.11 (D18)
BT81X.INT: U403.11 (INT_N); also elsewhere on the board
BT81X.PCLK: U403.39 (PCLK), U405.6 (CLK)
BT81X.R0: U403.1 (R0), U405.38 (D0)
BT81X.R1: U403.64 (R1), U405.40 (D1)
BT81X.R2: U403.63 (R2), U405.41 (D2)
BT81X.R3: U403.62 (R3), U405.42 (D3)
BT81X.R4: U403.61 (R4), U405.43 (D4)
BT81X.R5: U403.60 (R5), U405.44 (D5)
BT81X.R6: U403.59 (R6), U405.16 (D21)
BT81X.R7: U403.58 (R7), U405.17 (D22)
BT81X.VSYNC: U403.36 (VSYNC), U405.12 (D19)
CTP.RST: U407.11 (S4B); also elsewhere on the board
DISP_CS: J401.15; also elsewhere on the board
DISP_LED_A: C401.1, C402.1, D401.1 (K), D402.1 (K), J401.27
DISP_LED_K: C406.1, D402.2 (A), J401.29, R403.1, R404.1, R405.1, U401.3 (FB)
GND: C401.2, C402.2, C403.2, C404.2, C406.2, C408.2, C409.2, C410.2, C411.2, C412.2, C413.2, C414.2, C415.2, C416.2, C417.2, C418.2, C419.2, C420.2, C421.2, C422.2, C423.2, C424.2, C425.2, C426.2, C427.2, C428.2, C429.2, C430.2, C431.2, C432.2, C433.2, C434.2, C441.1, J401.8, J401.13, J401.14, J401.20, J401.25, J401.26, J402.1, J403.1, J404.1, JP402.1, R403.2, R404.2, R405.2, U401.2 (GND), U402.4 (GND), U403.23 (GND), U403.33 (GND), U403.48 (GND), U403.65 (EP), U404.4 (VSS), U404.9 (EP), U405.15 (GND), U405.24 (GND), U405.49 (DAP), U406.43 (GND), U407.6 (GND), U407.13 (/EN), Y401.3; also elsewhere on the board
GPIO_23: U407.8 (S3B); also elsewhere on the board
I2C0.SCL: U407.1 (S1B); also elsewhere on the board
I2C0.SDA: U407.4 (S2B); also elsewhere on the board
unnamed: C408.1, R406.2, U403.12 (PD_N)
unnamed: D401.2 (A), L401.2, U401.1 (SW)
unnamed: JP402.2, U405.39 (VOD_SEL)
unnamed: R401.2, U402.5 (2Y), U402.6 (3A), U402.7 (1Y)
unnamed: R402.2, U401.4 (/SHDN), U402.2 (3Y)
SPI1.MISO: J401.21, U403.4 (MISO/IO1); also elsewhere on the board
SPI1.MOSI: J401.19, U403.5 (MOSI/IO0); also elsewhere on the board
SPI1.SCK: J401.17, U403.3 (SCK); also elsewhere on the board
SPI1.SS3: R407.2, U403.6 (CS_N); also elsewhere on the board
iMX8.GPIO5.IO28: U407.9 (S3A); also elsewhere on the board
iMX8.GPIO5.IO29: U407.12 (S4A); also elsewhere on the board
iMX8.I2C3.SCL: U407.16 (S1A); also elsewhere on the board
iMX8.I2C3.SDA: U407.3 (S2A); also elsewhere on the board
iMX8.LVDS0.A0N: U406.18 (9B1); also elsewhere on the board
iMX8.LVDS0.A0P: U406.16 (8B1); also elsewhere on the board
iMX8.LVDS0.A1N: U406.25 (7B1); also elsewhere on the board
iMX8.LVDS0.A1P: U406.26 (6B1); also elsewhere on the board
iMX8.LVDS0.A2N: U406.29 (5B1); also elsewhere on the board
iMX8.LVDS0.A2P: U406.30 (4B1); also elsewhere on the board
iMX8.LVDS0.A3N: U406.38 (1B1); also elsewhere on the board
iMX8.LVDS0.A3P: U406.39 (0B1); also elsewhere on the board
iMX8.LVDS0.CLKN: U406.34 (3B1); also elsewhere on the board
iMX8.LVDS0.CLKP: U406.35 (2B1); also elsewhere on the board
iMX8.PWM1: U402.1 (1A); also elsewhere on the board

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
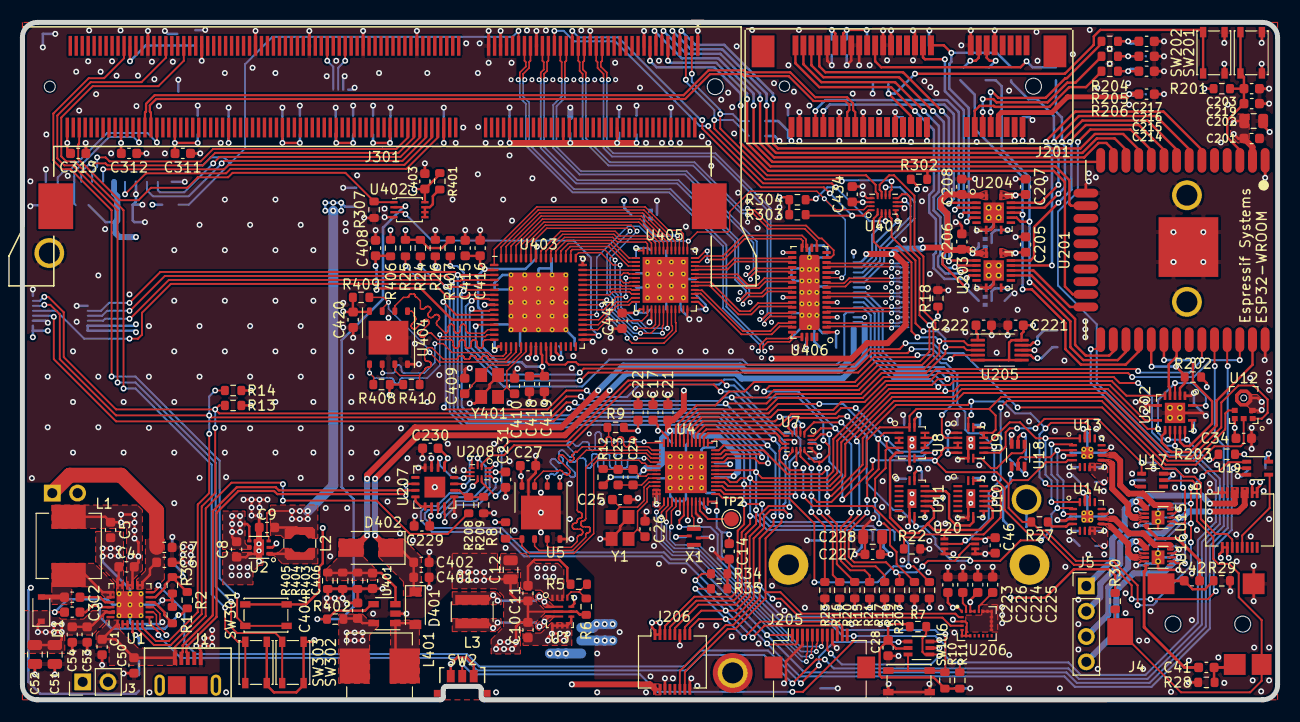
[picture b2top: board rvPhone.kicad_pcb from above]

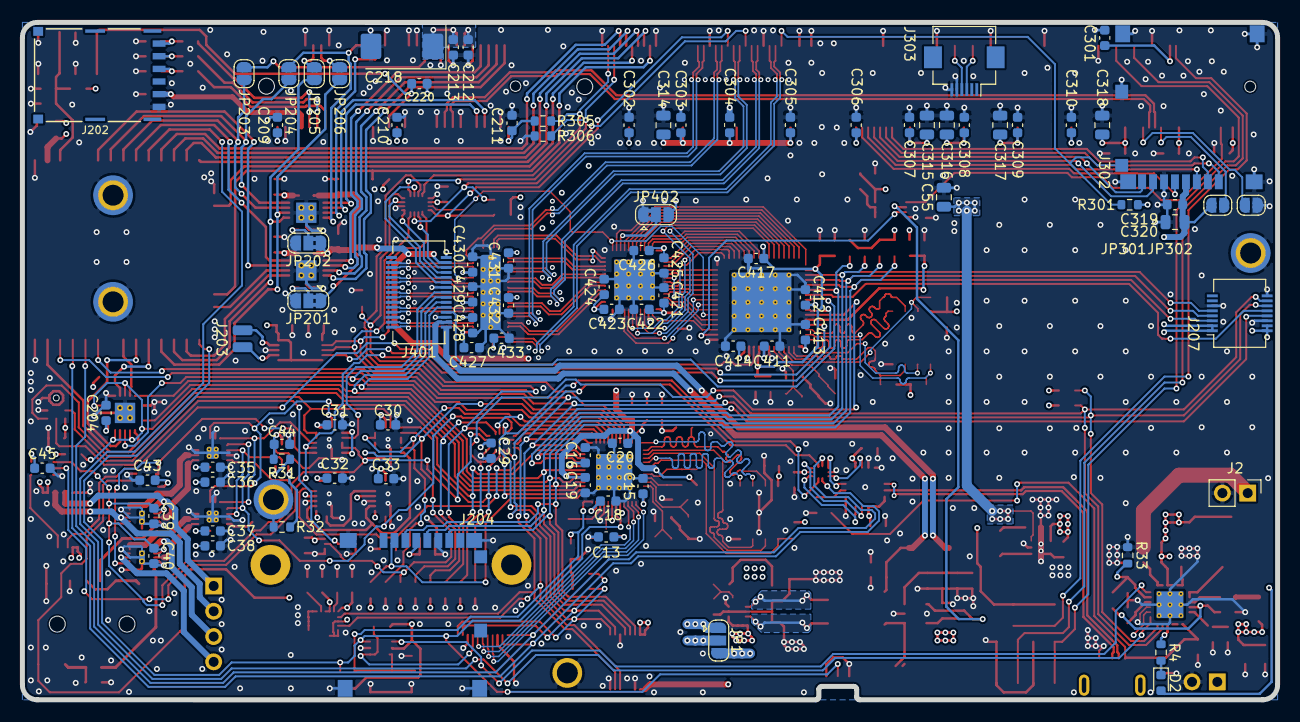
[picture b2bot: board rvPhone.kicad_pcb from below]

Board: 4 copper layers, 126.0 x 68.0 mm, 283 parts (94 on the bottom side), 258 nets.

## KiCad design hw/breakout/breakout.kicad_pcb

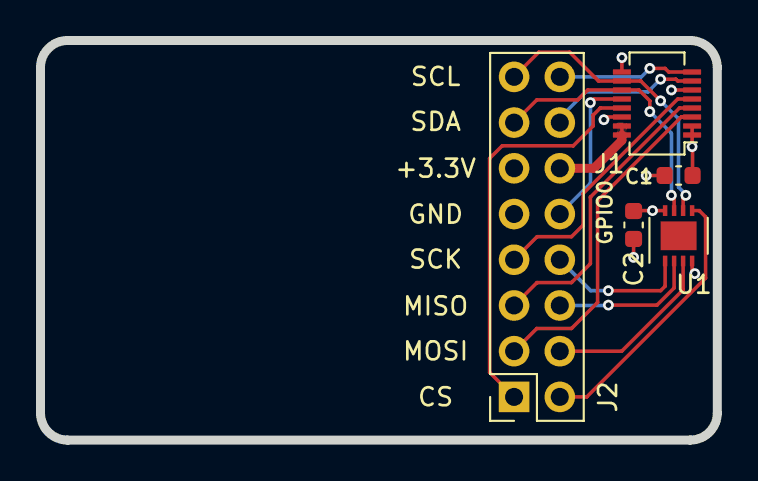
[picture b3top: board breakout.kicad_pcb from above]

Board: 4 copper layers, 37.6 x 22.2 mm, 5 parts (0 on the bottom side), 16 nets.

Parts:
C1: 10uF; C_0603_1608Metric
C2: 0.1uF; C_0603_1608Metric
J1: In; Molex_SlimStack_55560-0161_2x08_P0.50mm_Vertical
J2: Out; PinHeader_2x08_P2.54mm_Vertical
U1: PCA9536DP; WSON-8-1EP_3x3mm_P0.5mm_EP1.6x2.0mm

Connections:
+3V3: C1.1, C2.1, J1.1, J1.3, J2.11, U1.8
/GPIO0: J1.10, J2.10
/I2C_SCL: J1.14, J2.15, U1.6
/I2C_SDA: J1.12, J2.13, U1.7
/PCA_IO0: J2.8, U1.1
/PCA_IO1: J2.6, U1.2
/PCA_IO2: J2.4, U1.3
/PCA_IO3: J2.2, U1.5
/SPI_CS: J1.8, J2.1
/SPI_MISO: J1.7, J2.5
/SPI_MOSI: J1.5, J2.3
/SPI_SCK: J1.9, J2.7
/UART_RX: J1.15, J2.16
/UART_TX: J1.13, J2.14
GND: C1.2, C2.2, J1.6, J1.11, J1.16, J2.9, U1.4
VDD: J1.2, J1.4, J2.12
